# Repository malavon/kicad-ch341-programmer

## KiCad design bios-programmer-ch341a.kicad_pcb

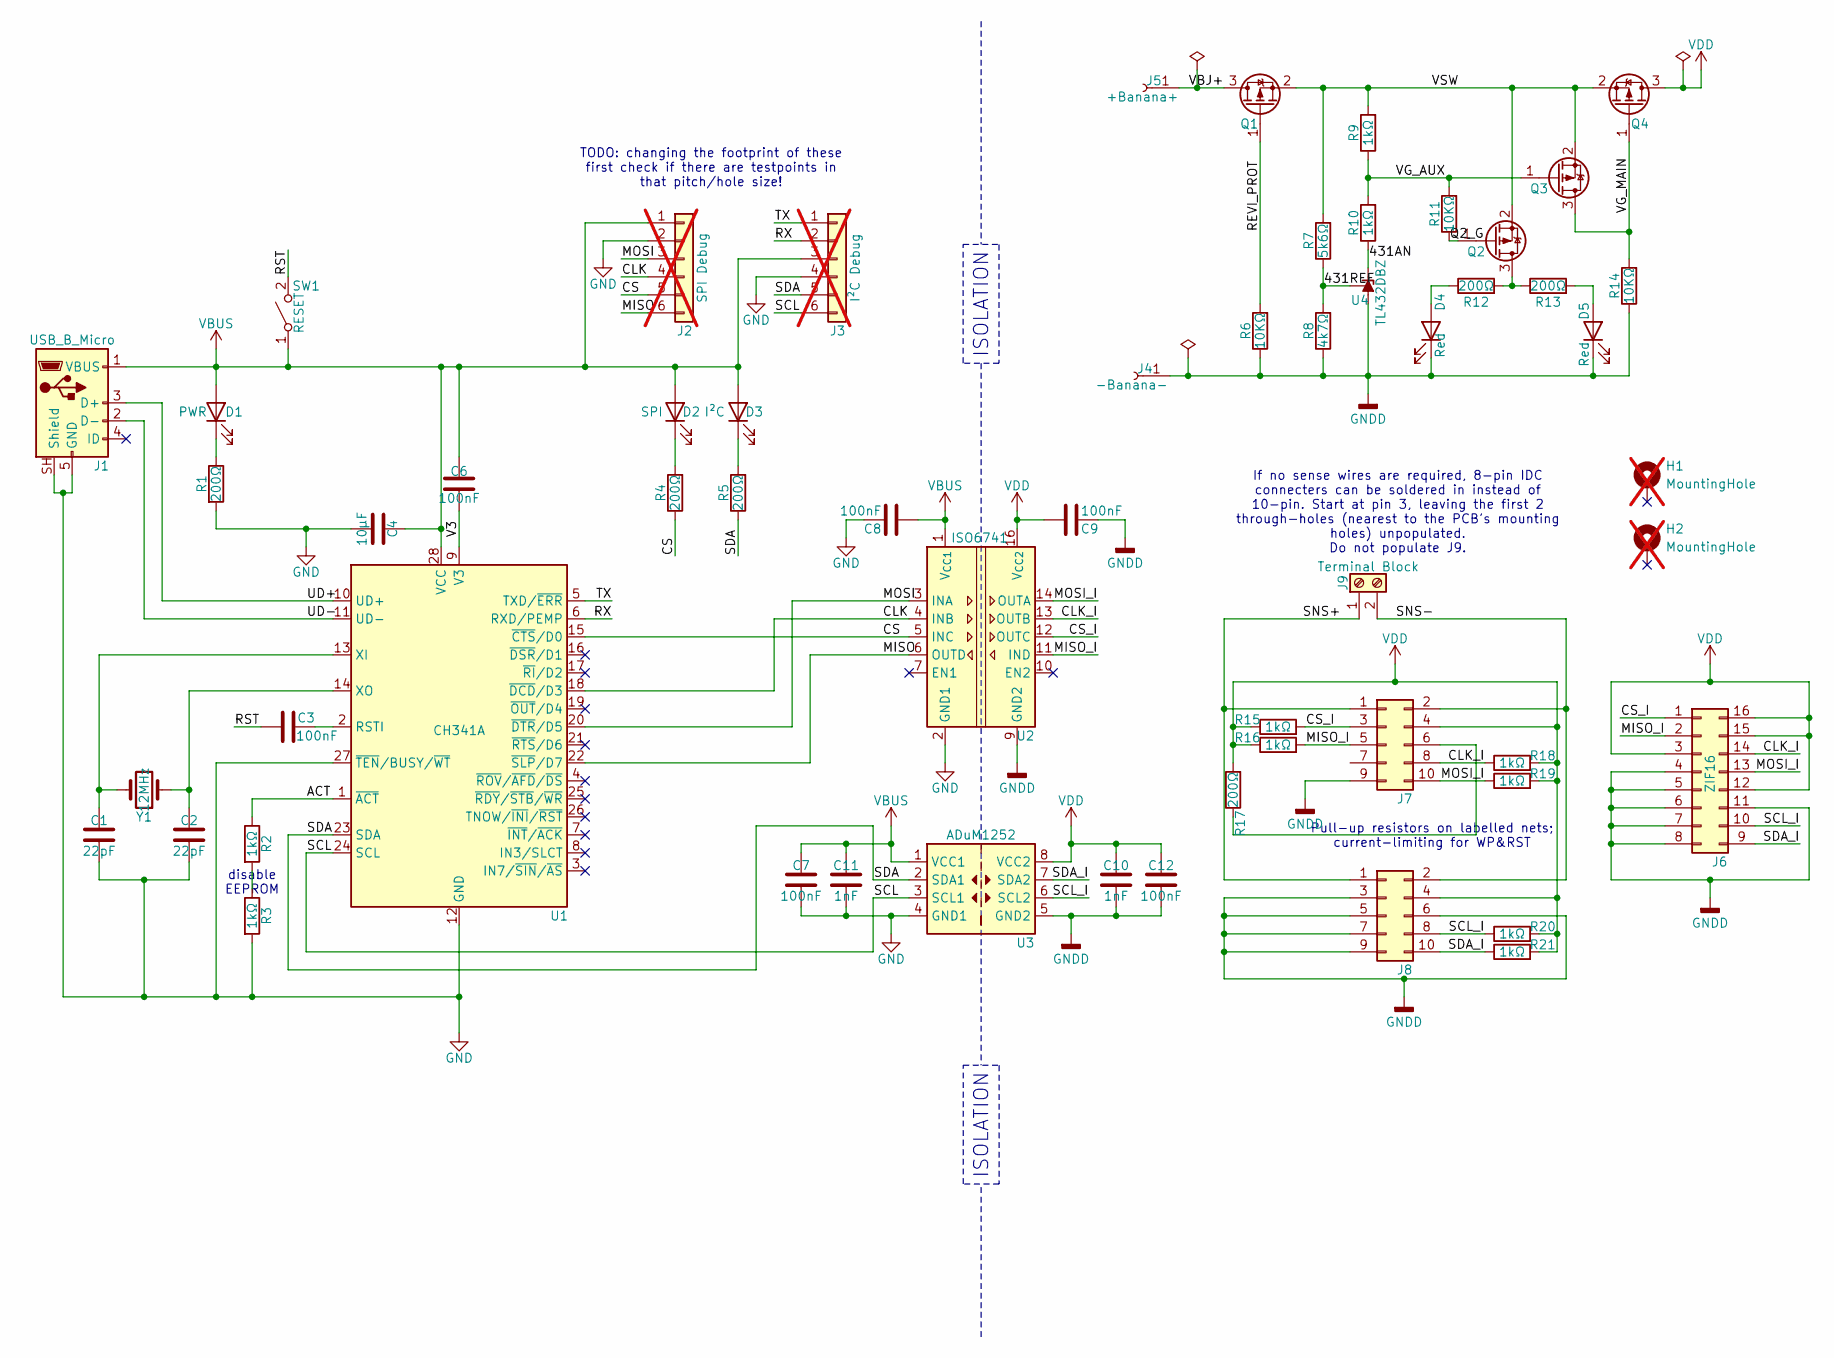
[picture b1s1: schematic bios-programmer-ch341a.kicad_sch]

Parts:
C1, C2: 22pF; C_0603_1608Metric_Pad1.08x0.95mm_HandSolder; Part KGM15ACG1H270GT
C3, C6, C7, C8, C9, C12: 100nF; C_0603_1608Metric_Pad1.08x0.95mm_HandSolder; Part CC0603KRX7R7BB104
C4: 10µF; C_0805_2012Metric; Part CL21A106KOQNNNF
C10, C11: 1nF; C_0603_1608Metric_Pad1.08x0.95mm_HandSolder; Part AC0603KRX7R0BB102
D1: Blue; LED_0603_1608Metric_Pad1.05x0.95mm_HandSolder; Part LTST-C194TBKT
D2, D3: YellowGreen; LED_0603_1608Metric_Pad1.05x0.95mm_HandSolder; Part HT-193UYG-5592
D4, D5: Red; LED_0805_2012Metric_Pad1.15x1.40mm_HandSolder; Part APT2012SURCK
H1, H2: MountingHole; MountingHole_2.2mm_M2_ISO14580_Pad_TopBottom; not fitted
J1: USB_B_Micro; USB_Micro-B_Amphenol_10118194-0001LF_Horizontal; Part 10118194(-0011LF)
J2: SPI Debug; PinSocket_1x06_P1.27mm_Vertical; not fitted
J3: I²C Debug; PinSocket_1x06_P1.27mm_Vertical; not fitted
J4: -Banana-; Banana_Cliff_FCR7350B_S16N-PC_Horizontal; Part FCR7350B
J5: +Banana+; Banana_Cliff_FCR7350R_S16N-PC_Horizontal; Part FCR7350R
J6: ZIF16; ZIF_Socket; Part 216-3340-00-0602J
J7, J8: IDC; IDC-Header_2x05_P2.54mm_Horizontal_1.64mm_pad; Part 61201021721
J9: Terminal Block; TerminalBlock_TE_282834-2_1x02_P2.54mm_Horizontal; Part TBC05-02-1-G-G
Q1, Q2, Q3, Q4: SSM3J328R; SOT-23; Part SSM3J328R
R1, R4, R5, R12, R13, R17: 200Ω; R_0603_1608Metric_Pad0.98x0.95mm_HandSolder; Part ERJ-3EKF2000V
R2, R3, R9, R10, R15, R16, R18, R19, R20, R21: 1kΩ; R_0603_1608Metric_Pad0.98x0.95mm_HandSolder; Part CQ03WAJ0102T5E
R6, R11, R14: 10KΩ; R_0603_1608Metric_Pad0.98x0.95mm_HandSolder; Part RC0603JR-0710KL
R7: 5k6Ω; R_0603_1608Metric_Pad0.98x0.95mm_HandSolder; Part RG1608P-562-D-T5
R8: 4k7Ω; R_0603_1608Metric_Pad0.98x0.95mm_HandSolder; Part RG1608P-472-D-T5
SW1: SPST; SW_Tactile_SPST_NO_Straight_CK_PTS636Sx25SMTRLFS; Part PTS636SKG25SMTR LFS
U1: CH341A; SOIC-28W_7.5x17.9mm_P1.27mm; Part CH341(A|B)
U2: ISO6741; SOIC-16W_7.5x10.3mm_P1.27mm; Part ISO6741DWR
U3: ADuM1252; SOIC-8_3.9x4.9mm_P1.27mm; Part ADUM1252ASA+
U4: TL432DBZ; SOT-23; Part TL432LIBCDBZ
Y1: 12MHz; Crystal_HC49-4H_Vertical; Part ABL-12.000MHZ-B2

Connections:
/431AN: R10.1, U4.2 (K)
/431REF: R7.1, R8.2, U4.1 (REF)
/ACT: R2.1, U1.1 (~ACT)
/CLK: J2.4, U1.18 (~DCD/D3), U2.4 (INB)
/CLK_I: J6.14, J7.8, R18.1, U2.13 (OUTB)
/CS: J2.5, R4.1, U1.15 (~CTS/D0), U2.5 (INC)
/CS_I: J6.1, J7.3, R15.2, U2.12 (OUTC)
/MISO: J2.6, U1.22 (~SLP/D7), U2.6 (OUTD)
/MISO_I: J6.2, J7.5, R16.2, U2.11 (IND)
/MOSI: J2.3, U1.20 (~DTR/D5), U2.3 (INA)
/MOSI_I: J6.13, J7.10, R19.1, U2.14 (OUTA)
/Q2_G: Q2.1 (G), R11.1
/REVI_PROT: Q1.1 (G), R6.2
/RST: C3.2, SW1.2 (B)
/RX: J3.2, U1.6 (RXD/PEMP)
/SCL: J3.6, U1.24 (SCL), U3.3 (SCL1)
/SCL_I: J6.10, J8.8, R20.1, U3.6 (SCL2)
/SDA: J3.5, R5.1, U1.23 (SDA), U3.2 (SDA1)
/SDA_I: J6.9, J8.10, R21.1, U3.7 (SDA2)
/SNS+: J7.1, J8.1, J9.1
/SNS-: J7.2, J8.2, J9.2
/TX: J3.1, U1.5 (TXD/~ERR)
/UD+: J1.3 (D+), U1.10 (UD+)
/UD-: J1.2 (D-), U1.11 (UD-)
/V3: C6.2, U1.9 (V3)
/VBJ+: J5.1 (Pin_1_1), Q1.3 (D)
/VG_AUX: Q3.1 (G), R9.1, R10.2, R11.2
/VG_MAIN: Q3.3 (D), Q4.1 (G), R14.2
/VSW: Q1.2 (S), Q2.2 (S), Q3.2 (S), Q4.2 (S), R7.2, R9.2
GND: C1.2, C2.2, C4.2, C7.2, C8.2, C11.2, J1.5 (GND), J1.SH (Shield), J2.2, J3.4, R1.2, R3.2, U1.12 (GND), U1.27 (~TEN/BUSY/~WT), U2.2 (GND1), U2.8 (GND1), U3.4 (GND1)
GNDD: C9.1, C10.2, C12.2, D4.1 (K), D5.1 (K), J4.1 (Pin_1_1), J6.4, J6.5, J6.6, J6.7, J6.8, J6.11, J7.9, J8.3, J8.5, J8.6, J8.7, J8.9, R6.1, R8.1, R14.1, U2.9 (GND2), U2.15 (GND2), U3.5 (GND2), U4.3 (A)
unnamed: D1.1 (K), R1.1
unnamed: D2.1 (K), R4.2
unnamed: D3.1 (K), R5.2
unnamed: D4.2 (A), R12.1
unnamed: D5.2 (A), R13.2
unnamed: Q2.3 (D), R12.2, R13.1
unnamed: R2.2, R3.1
unnamed: C3.1, U1.2 (RSTI)
unnamed: C1.1, U1.13 (XI), Y1.2
unnamed: C2.1, U1.14 (XO), Y1.1
VBUS: C4.1, C6.1, C7.1, C8.1, C11.1, D1.2 (A), D2.2 (A), D3.2 (A), J1.1 (VBUS), J2.1, J3.3, SW1.1 (A), U1.28 (VCC), U2.1 (V_{CC1}), U3.1 (VCC1)
VDD: C9.2, C10.1, C12.1, J6.3, J6.12, J6.15, J6.16, J7.4, J8.4, Q4.3 (D), R15.1, R16.1, R17.2, R18.2, R19.2, R20.2, R21.2, U2.16 (V_{CC2}), U3.8 (VCC2)

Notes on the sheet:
disable EEPROM
TODO: changing the footprint of these first check if there are testpoints in that pitch/hole size!
If no sense wires are required, 8-pin IDC connecters can be soldered in instead of 10-pin. Start at pin 3, leaving the first 2 through-holes (nearest to the PCB's mounting holes) unpopulated. Do not populate J9.
ISOLATION
Pull-up resistors on labelled nets; current-limiting for WP&RST

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
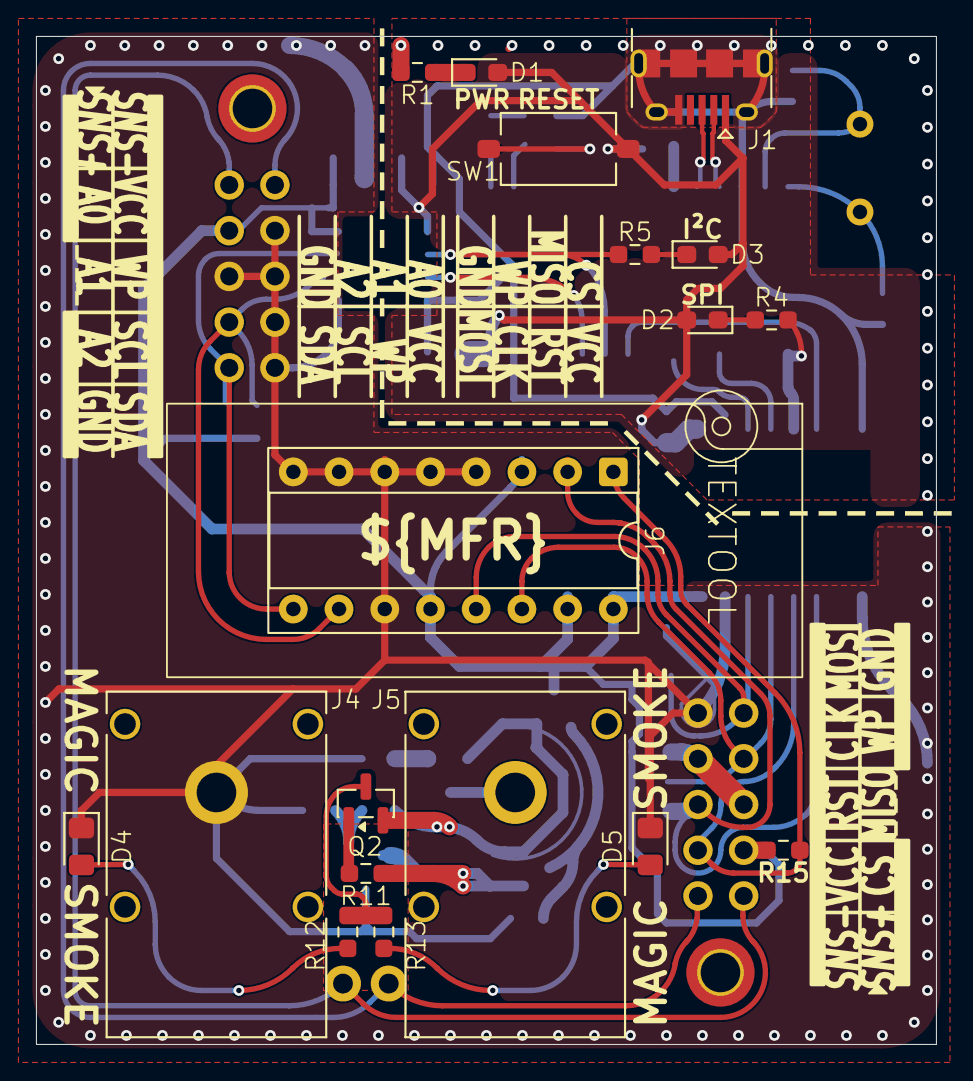
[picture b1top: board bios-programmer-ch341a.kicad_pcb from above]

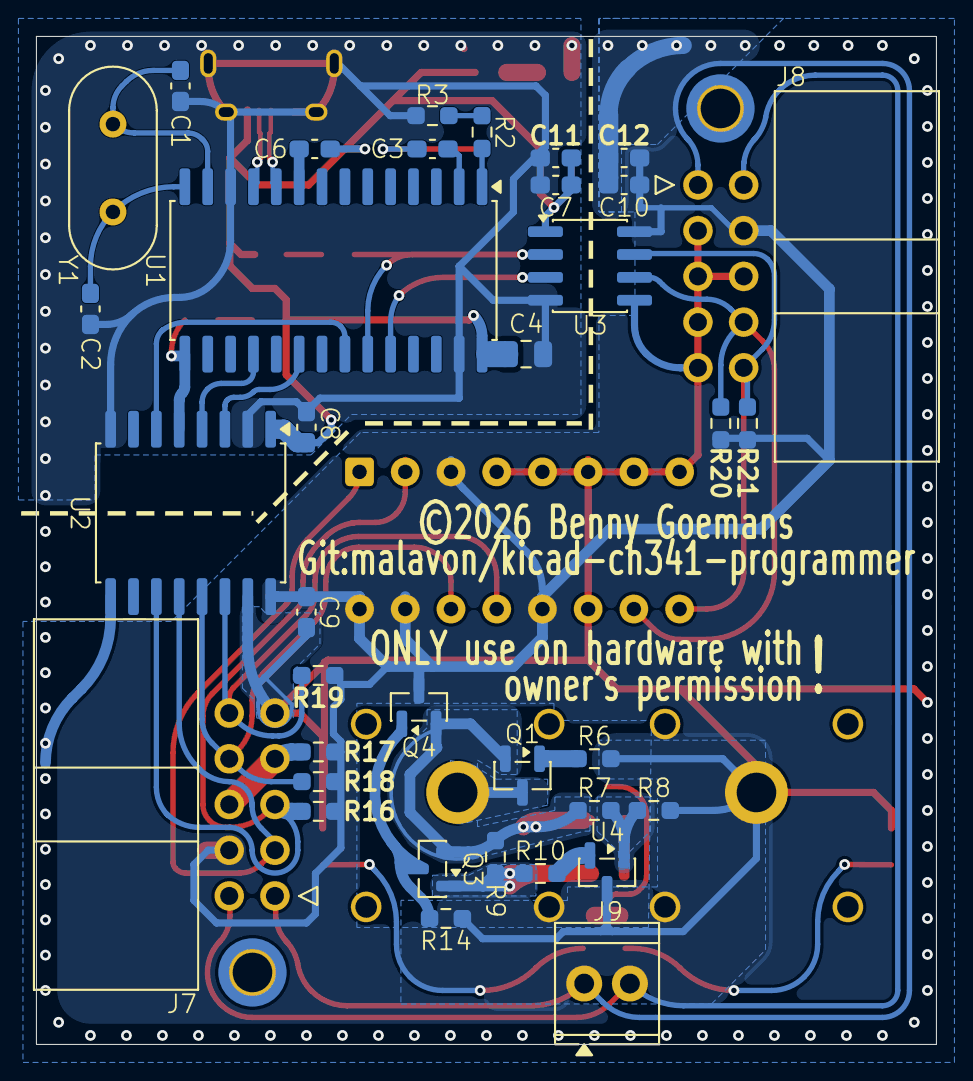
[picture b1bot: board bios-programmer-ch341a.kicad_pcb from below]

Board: 2 copper layers, 50.0 x 56.0 mm, 56 parts (36 on the bottom side), 42 nets.

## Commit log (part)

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2026-04-14 Removed voltage regulator, running from VBUS directly + dual status LEDs
    I left the debug headers intact for now but that's next up.
    Having dual LEDs as status LED is rather useful, I could have these next to the
    ZIF socket to notify the user which one is getting used. It might prevent some
    user errors.
    Note: future (alternatives) will probably not use a ZIF socket but connect to a
    clip through a ribbon wire. OR I may decide to put it all on a single PCB.
2026-04-14 Added a reset switch and removed RST & ACT signals from debug headers
    The reset is probably useful, I've had plenty of times that one of these CH341
    chips or the chip under programming stopped responding because something went
    wrong with the software.
    No need to unplug the USB all the time, reset switches should be more omni-
    present.
    Those 2 extra signals aren't really needed for debugging if there's a switch,
2026-04-14 (Issues fixed as well... DRC) Isolated version schematics, initial versions
    It's more than likely that the isolation pinout will change for easier routing.
    All DRC rules are passed EXCEPT one: SCL connection complains that it's not
    connected to power on the ZIF socket. Either this is a DRC mishap, or something
    is actually wrong with the idea or the isolator used.
    Note: isolator part numbers are expected to change, hopefully pinout doesn't.
    It's possibly I decide to use a 4 or 6-channel isolator instead of 3 dual ones.
2026-04-14 Notes after reading the CH341 datasheet & crystal package
    The todo list has been expanded with both additions and simplifications. I'll
    be running the CH341 on 5V since it never connects directly to any chip.
    It would also be perfectly fine to provide less capacitance if there's no real
    load on the device, especially no chance of a surge current on the USB bus.
    All programming load will be monitored by the external connection anyway.
2026-04-14 Correct isolator types
    Initially I was hoping to re-use isolation for both the I2C & SPI memory types.
    In short, I require 1.8V operation on at least one side. This is already hard
    to find in I2C regulators (e.g. TI does only 2.25V parts).
    However, the I2C parts are considerably more expensive, so reusing those would
    more than double the price (in total). On top of that, they only support speeds
    up to 2MHz.
2026-04-14 PCB: Fixed the ZIF socket layout, pin 1 is pin 1 on SPI (NOT EEPROM)
    I still keep the 25/24 order simply because the layout gets much worse if I
    change these up. There will be a very clear silkscreen explaining which chip
    goes in which part of the socket (including the pinout).
    PROBLEM: I did notice that one the left side of the PCB there's GND and GNDD
    overlapping each other. Unless I can fix this easily another way, I can only
    see one possible fix: place U3 (I2C isolator) in-between the J8 (IDC connector)
2026-04-14 PCB redesign, reducing footprint & optimizing layout
    IMPORTANT: I've switched up the footprint of the ZIF socket (will require
    doublechecking) in order to improve the routing.
    All in all I'm pretty content with this layout idea, routing goes well and most
    of the important parts have been routed in this example.
    However, due to the orientation of the CH341 it will be difficult to route the
    USB data signals. Since these are high-speed - the highest of all signals on
2026-04-14 First layout test & opt for 2 IPC connectors instead of 4
    This layout is very preliminary and I'm committing this because I want to try
    out a different layout.
    Using 2 IPC connectors is probably best:
    * still provides support when used diagonally - at least I expect them to
    * no branching of signals, just one long string crossing THROUGH the ZIF socket
    Note that I'm having some troubles with the USB connection, D+ & D- are in the
2026-04-15 PCB: moved ISO6741 more inwards
    Originally pins for the socket came out much further since it was oriented
    differently and - I think - I kept it this far to the side just by coincidence.
2026-04-15 PCB: isolated GND on top and isolated power at the bottom
    The other way around results in messier routing and the PCB is big enough to
    have a few tracks around to provide power, which are then usurped into zones.
    Note that I have a habit - for the 4 pcb's I've more or less designed - of
    connecting all pins before going into zones. Zones might be a useful tool to
    see if routing is possible, but I prefer it this way because it makes me think
    more about the layout and its consequences.
2026-04-15 PCB: routed VBUS at the bottom, GND on top
    I tried it the other way around with VBUS on top and GND on the bottom side,
    but this resulted in pretty annoying jumps & vias. This one is cleaner, there's
    only one overjump to be made.
2026-04-15 TEMP: overvoltage idea; correct? better options?
2026-04-15 prolly temp: cleaned up DRC errors, moved silkscreens/vias where need be but going to move a few IC's ... breaking all tracks and creating more errors
2026-04-17 3D: model of the ZIF socket
    This model is embedded in the footprint that I made, which I prefer. But it's
    good to keep the model in the repo as well, just to be complete.
    Note that this was originally a parasolid .x_t file, which I managed to convert
    using an online converter. Apparently no open-source solutions exist?
2026-04-17 temporary outputs for linking
2026-04-18 PCB: cleaned up DRC errors & moved silkscreens/vias neater
    Not that it matters much because while doing this I noticed it might be better
    to move a few IC's, including the CH341. This will mean all tracks are moved as
    well, breaking a lot of things.
    Definitely one of the things Kicad doesn't exactly excel at.
    prolly temp: cleaned up DRC errors, moved silkscreens/vias where need be
    but going to move a few IC's ... breaking all tracks and creating more errors
2026-04-18 forum
2026-04-27 EXPORT: exporting using script & kicad-cli
    The CLI has more options than the jobsets do, or at least the jobsets' UI has.
    It's not the most efficient option since it has to re-read the project each for
    each export.
2026-04-27 SIM: models for a few zener diodes and P-channel MOSFETs
2026-04-27 SIM: changing components to to library ones, output voltage goes above 6V
    Using library components ensures that there are no mistakes in the models.
    In this case ChatGPT was actually useful in noticing errors, although QUCS-S
    does seem to use 'M' for 'milli' instead of 'mega' as it should? Odd.
    Using these models the output voltage is allowed to go over 6V, which is rather
    high. This could be alleviated using a 5.1V Zener diode presumably.
2026-04-27 SCH: moving the simulated power protection circuit into Kicad
2026-04-27 SCH: updated protection circuit to some simulation changes; TODO explain? 5.6K gone; 220O on LED only, ok for low voltage
2026-04-27 PCB temp overvolt; still tryign to get better layout and in progress; squashed; TODO message
    pcb almost goeie plaatsing ...
    pcb reasonable; ziet er ok uit? maar LEDs nog
2026-04-27 tl432! footprint best, zones for gnd on bottom & vgsomething?
2026-04-27 PCB: power path protection reasonable layout TODO
    probably final version including power-path protection TODO explain some more? first check previous commit, rebase etc
    different mosfet! Toshiba thingy
    zones for almost everything
    wider tracks
    and yeah, accidental symbol ...
2026-05-01 pcb temp almost done; the only thing I don't like is the GND bridge
2026-05-01 PCB: moved OVP LED tracks down, added LED resistor and some beautification
2026-05-01 PCB: moving stuff; more GND
2026-05-01 silkscreen table + some improvements
2026-05-01 pcb silkscreen Anonymous Pro text disregard kicad check for TT font width; kicd font is thinner and not detected
2026-05-01 PCB: silkscreen in metric & font taller than wide
    I think it looks kinda good with a much taller than wide font.
    Text boxes were replaced with text components which are much easier to position
    as intented. It is still difficult to get good text positioning/sizing in Kicad
    and having separate components works around this.
2026-05-01 pcb kicad font for value of leds
2026-05-01 temp forum
2026-05-01 pcb vias & slikscreen fixes sda/scl
2026-05-05 SCH: off-the-shelf CH341a programmer
    Typical CH341a programmer, based on a schematic I found on or via EEVBlog.
    It groups all capacitors at the moment, but that's fine. Capacitances will need
    to change anyway. I didn't use a resistor network like the programmer does, but
    nothing stops me from changing this later on.
2026-05-05 PCB: IDC connector on the bottom, also functioning as standoffs
    The idea is that a chip can be programmed through the ZIF socket or by connect-
    ing a cable with a in-place programming clip.
    This may however lead to issues and in hindsight it might become a questionable
    decision: the high-speed signals will be branched and lead nowhere, which may
    lead to reflections and thus signal integrity failure.
    The cheap CH341 programmers do not use separate IDC connectors but instead
2026-05-10 EXPORT: initial script
2026-05-10 SCH: added some part numbers
    Some part numbers have many possibilities, like 5% resistors. I assign these
    simply based on what I have in stock, sometimes using a more expensive one that
    uses up some of my (already very small) stock.
2026-05-10 SCH/PCB: adding sense wires & some beautification
    Rationale: sense wires are not strictly necessary and the design would work
    perfectly without. It does however add some indication of the voltage as it is
    present on the IC under program through the IDC connectors. It is after all an
    unknown how long and thick the wires leading up to this IC are.
    That said, it wouldn't provide any insight in any voltage drop on the actual
    data lines and as such provide less information than really required.
2026-05-10 PCB: embedded font "Anonymous Pro", used for the silkscreen (except references)
    Embedding fonts seems like a good idea, since there's no knowing if everyone
    who could potentially ever open this project have this font.
2026-05-10 PCB: moving stuff; more GND; pcb all is well; before I increase clearance TODO
2026-05-10 PCB/SCH: separate field Label for PCB label & sort manufacturer/part #s
    Using "Value" for the PCB label isn't terrible, but at the same time it's not
    really "locked down" as a separate label. There's no reason Value can't be used
    for something to indicate a certain message to the user in the schematics.
    It's also not clear for anyone looking at the schematics that that specific
    text is used on the PCB.
    Splitting up removes any ambiguity.
2026-05-10 PCB: routing/beautification of tracks
    Yup, this time I used arcs to get around the through-hole footprint of the IDC
    connector J7 (SPI) on the bottom layer. It's actually faster and makes it so
    much nicer to look at. No more crooked tracks (there).
2026-05-10 PCB: reset text "above" button
    "Above" because in reality the board is really upside down, but I don't want
    to turn the board and then have all other commits have the board upside down.
    That said, there is no definite up or down to the board, it's just that the
    banana jacks would most logically never be oriented towards the person using
    the programmer.
2026-05-10 PCB: rerouted SCL for more clearance; fixed reference J9 silkscreen
    It's strictly not necessary, but not going in-between the two connector pins
    adds some clearance. It won't hurt in any way.
2026-05-10 SCH/PCB: 200Ohm current limiting resistor part numbers updated
2026-05-10 3D: replaced the USB model by Digikey-downloaded model
    The model I downloaded from the Amphenol website doesn't have any colour info
    in it, which for some strange reason ends up in a very annoying cyan-like shade.
    The digikey model has normal colouring information and thus looks nicer.

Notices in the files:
bios-programmer-ch341a.kicad_pcb:
©2026 Benny Goemans
